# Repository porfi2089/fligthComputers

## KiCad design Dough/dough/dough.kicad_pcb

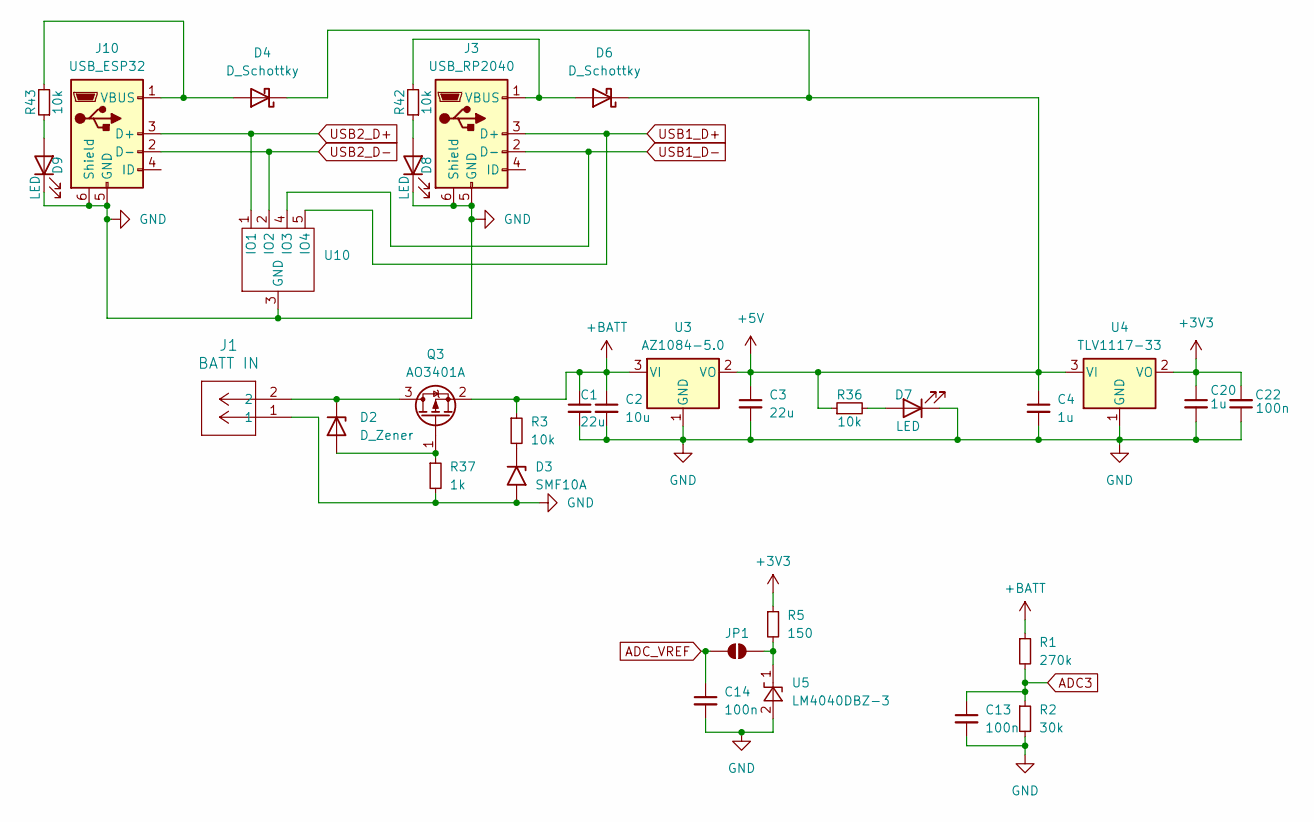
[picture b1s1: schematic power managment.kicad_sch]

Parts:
C1, C3: 22u; C_0603_1608Metric_Pad1.08x0.95mm_HandSolder
C2: 10u; C_0603_1608Metric_Pad1.08x0.95mm_HandSolder
C4, C20: 1u; C_0603_1608Metric_Pad1.08x0.95mm_HandSolder
C13, C14, C22: 100n; C_0603_1608Metric_Pad1.08x0.95mm_HandSolder
D2: D_Zener; D_SOD-123
D3: SMF10A; D_SMF
D4, D6: D_Schottky; D_SOD-323_HandSoldering
D7, D8, D9: LED; LED_0603_1608Metric_Pad1.05x0.95mm_HandSolder
J1: BATT IN; CONN2_H-B-02-TS_ADM
J3: USB_RP2040; USB_Micro-B_Amphenol_10118194_Horizontal
J10: USB_ESP32; USB_Micro-B_Amphenol_10118194_Horizontal
JP1: SolderJumper-2_P1.3mm_Open_TrianglePad1.0x1.5mm
Q3: AO3401A; SOT-23_Handsoldering
R1: 270k; R_0603_1608Metric_Pad0.98x0.95mm_HandSolder
R2: 30k; R_0603_1608Metric_Pad0.98x0.95mm_HandSolder
R3, R36, R42, R43: 10k; R_0603_1608Metric_Pad0.98x0.95mm_HandSolder
R5: 150; R_0603_1608Metric_Pad0.98x0.95mm_HandSolder
R37: 1k; R_0603_1608Metric_Pad0.98x0.95mm_HandSolder
U3: AZ1084-5.0; TO-252-3_TabPin2
U4: TLV1117-33; SOT-223-3_TabPin2
U5: LM4040DBZ-3; SOT-23
U10: 10-UFDNF(2.5mm-1mm)

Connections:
+3V3: C20.1, C22.2, R5.1, U4.2 (VO); also elsewhere on the board
+5V: C3.1, C4.1, D4.1 (K), D6.1 (K), R36.1, U3.2 (VO), U4.3 (VI); also elsewhere on the board
+BATT: C1.1, C2.1, Q3.2 (S), R1.1, R3.1, U3.3 (VI); also elsewhere on the board
ADC3: C13.1, R1.2, R2.1; also elsewhere on the board
ADC_VREF: C14.1, JP1.1 (A); also elsewhere on the board
unnamed: D2.2 (A), Q3.1 (G), R37.1
unnamed: D2.1 (K), J1.2, Q3.3 (D)
unnamed: D3.1 (A1), R3.2
unnamed: D4.2 (A), J10.1 (VBUS), R43.2
unnamed: D6.2 (A), J3.1 (VBUS), R42.2
unnamed: D7.2 (A), R36.2
unnamed: D8.2 (A), R42.1
unnamed: D9.2 (A), R43.1
unnamed: JP1.2 (B), R5.2, U5.1 (K)
USB1_D+: J3.3 (D+), U10.5 (IO4); also elsewhere on the board
USB1_D-: J3.2 (D-), U10.4 (IO3); also elsewhere on the board
USB2_D+: J10.3 (D+), U10.1 (IO1); also elsewhere on the board
USB2_D-: J10.2 (D-), U10.2 (IO2); also elsewhere on the board

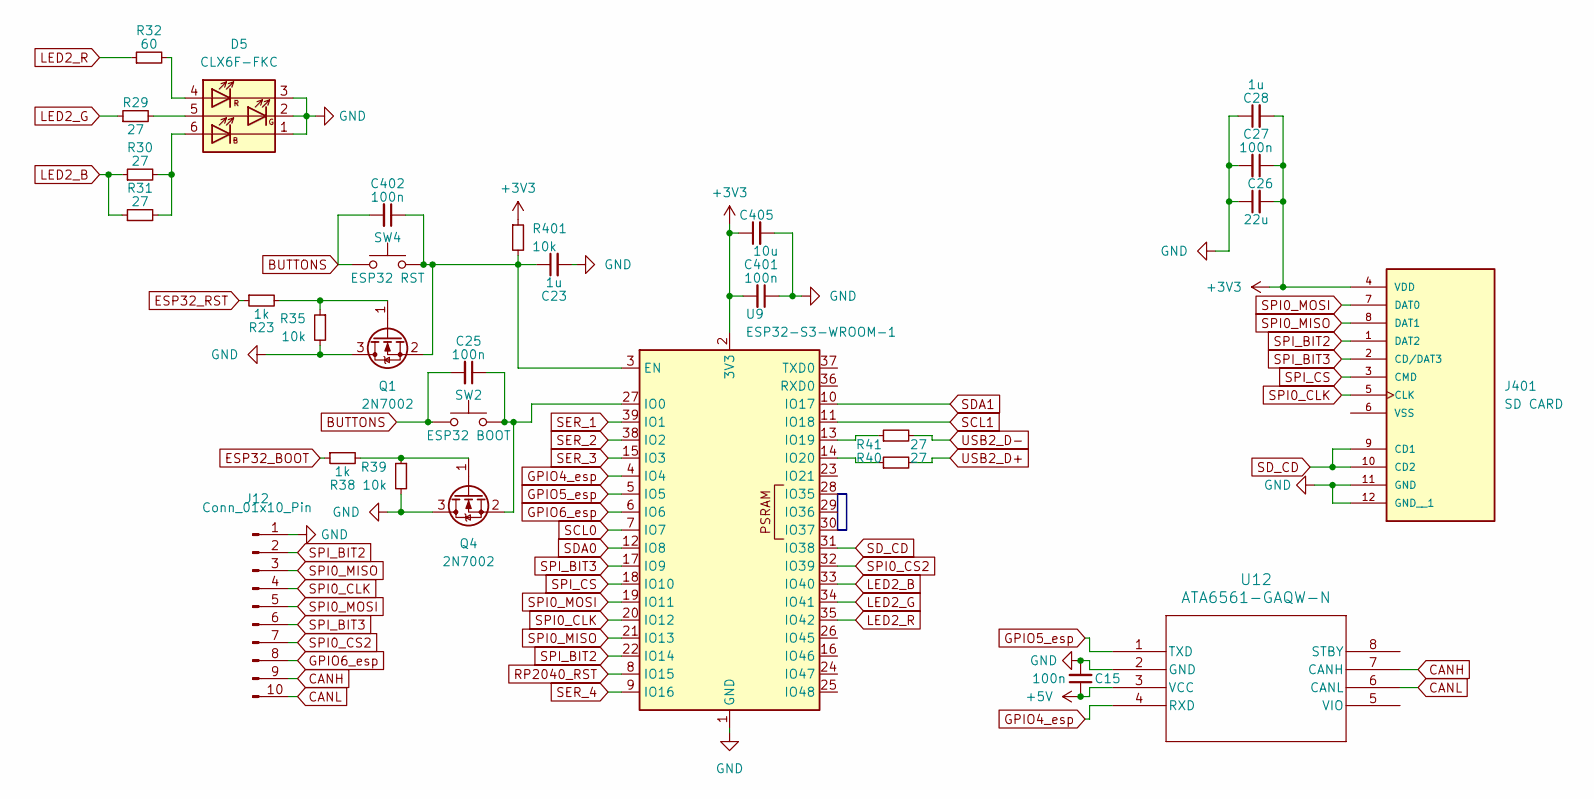
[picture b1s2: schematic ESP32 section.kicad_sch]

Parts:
C15, C25, C27, C401, C402: 100n; C_0603_1608Metric_Pad1.08x0.95mm_HandSolder
C23, C28: 1u; C_0603_1608Metric_Pad1.08x0.95mm_HandSolder
C26: 22u; C_0603_1608Metric_Pad1.08x0.95mm_HandSolder
C405: 10u; C_0603_1608Metric_Pad1.08x0.95mm_HandSolder
D5: CLX6F-FKC; LED_RGB_PLCC-6
J12: Conn_01x10_Pin; PinHeader_1x10_P2.54mm_Vertical
J401: SD CARD; MSD11_card_conn
Q1, Q4: 2N7002; SOT-23
R23, R38: 1k; R_0603_1608Metric_Pad0.98x0.95mm_HandSolder
R29, R30, R31, R40, R41: 27; R_0603_1608Metric_Pad0.98x0.95mm_HandSolder
R32: 60; R_0603_1608Metric_Pad0.98x0.95mm_HandSolder
R35, R39, R401: 10k; R_0603_1608Metric_Pad0.98x0.95mm_HandSolder
SW2: ESP32 BOOT; SW_Tactile_SPST_NO_Straight_CK_PTS636Sx25SMTRLFS
SW4: ESP32 RST; SW_Tactile_SPST_NO_Straight_CK_PTS636Sx25SMTRLFS
U9: ESP32-S3-WROOM-1
U12: ATA6561-GAQW-N; SOIC8_4P9X3P9MC_MCH

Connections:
+3V3: C26.2, C27.1, C28.2, C401.2, C405.1, J401.4 (VDD), R401.1, U9.2 (3V3); also elsewhere on the board
+5V: C15.1, U12.3 (VCC); also elsewhere on the board
BUTTONS: C25.2, C402.2, SW2.1, SW4.1; also elsewhere on the board
CANH: J12.9, U12.7 (CANH)
CANL: J12.10, U12.6 (CANL)
ESP32_BOOT: R38.1; also elsewhere on the board
ESP32_RST: R23.1; also elsewhere on the board
GPIO4_esp: U9.4 (IO4), U12.4 (RXD)
GPIO5_esp: U9.5 (IO5), U12.1 (TXD)
GPIO6_esp: J12.8, U9.6 (IO6)
LED2_B: R30.1, R31.1, U9.33 (IO40)
LED2_G: R29.1, U9.34 (IO41)
LED2_R: R32.1, U9.35 (IO42)
unnamed: D5.6 (AB), R30.2, R31.2
unnamed: D5.5 (AG), R29.2
unnamed: D5.4 (AR), R32.2
unnamed: C23.1, C402.1, Q1.2 (S), R401.2, SW4.2, U9.3 (EN)
unnamed: C25.1, Q4.2 (S), SW2.2, U9.27 (IO0)
unnamed: R41.1, U9.13 (IO19)
unnamed: R40.1, U9.14 (IO20)
RP2040_RST: U9.8 (IO15); also elsewhere on the board
SCL0: U9.7 (IO7); also elsewhere on the board
SCL1: U9.11 (IO18); also elsewhere on the board
SDA0: U9.12 (IO8); also elsewhere on the board
SDA1: U9.10 (IO17); also elsewhere on the board
SD_CD: J401.9 (CD1), J401.10 (CD2), U9.31 (IO38)
SER_1: U9.39 (IO1); also elsewhere on the board
SER_2: U9.38 (IO2); also elsewhere on the board
SER_3: U9.15 (IO3); also elsewhere on the board
SER_4: U9.9 (IO16); also elsewhere on the board
SPI0_CLK: J12.4, J401.5 (CLK), U9.20 (IO12)
SPI0_CS2: J12.7, U9.32 (IO39)
SPI0_MISO: J12.3, J401.8 (DAT1), U9.21 (IO13)
SPI0_MOSI: J12.5, J401.7 (DAT0), U9.19 (IO11)
SPI_BIT2: J12.2, J401.1 (DAT2), U9.22 (IO14)
SPI_BIT3: J12.6, J401.2 (CD/DAT3), U9.17 (IO9)
SPI_CS: J401.3 (CMD), U9.18 (IO10)
USB2_D+: R40.2; also elsewhere on the board
USB2_D-: R41.2; also elsewhere on the board

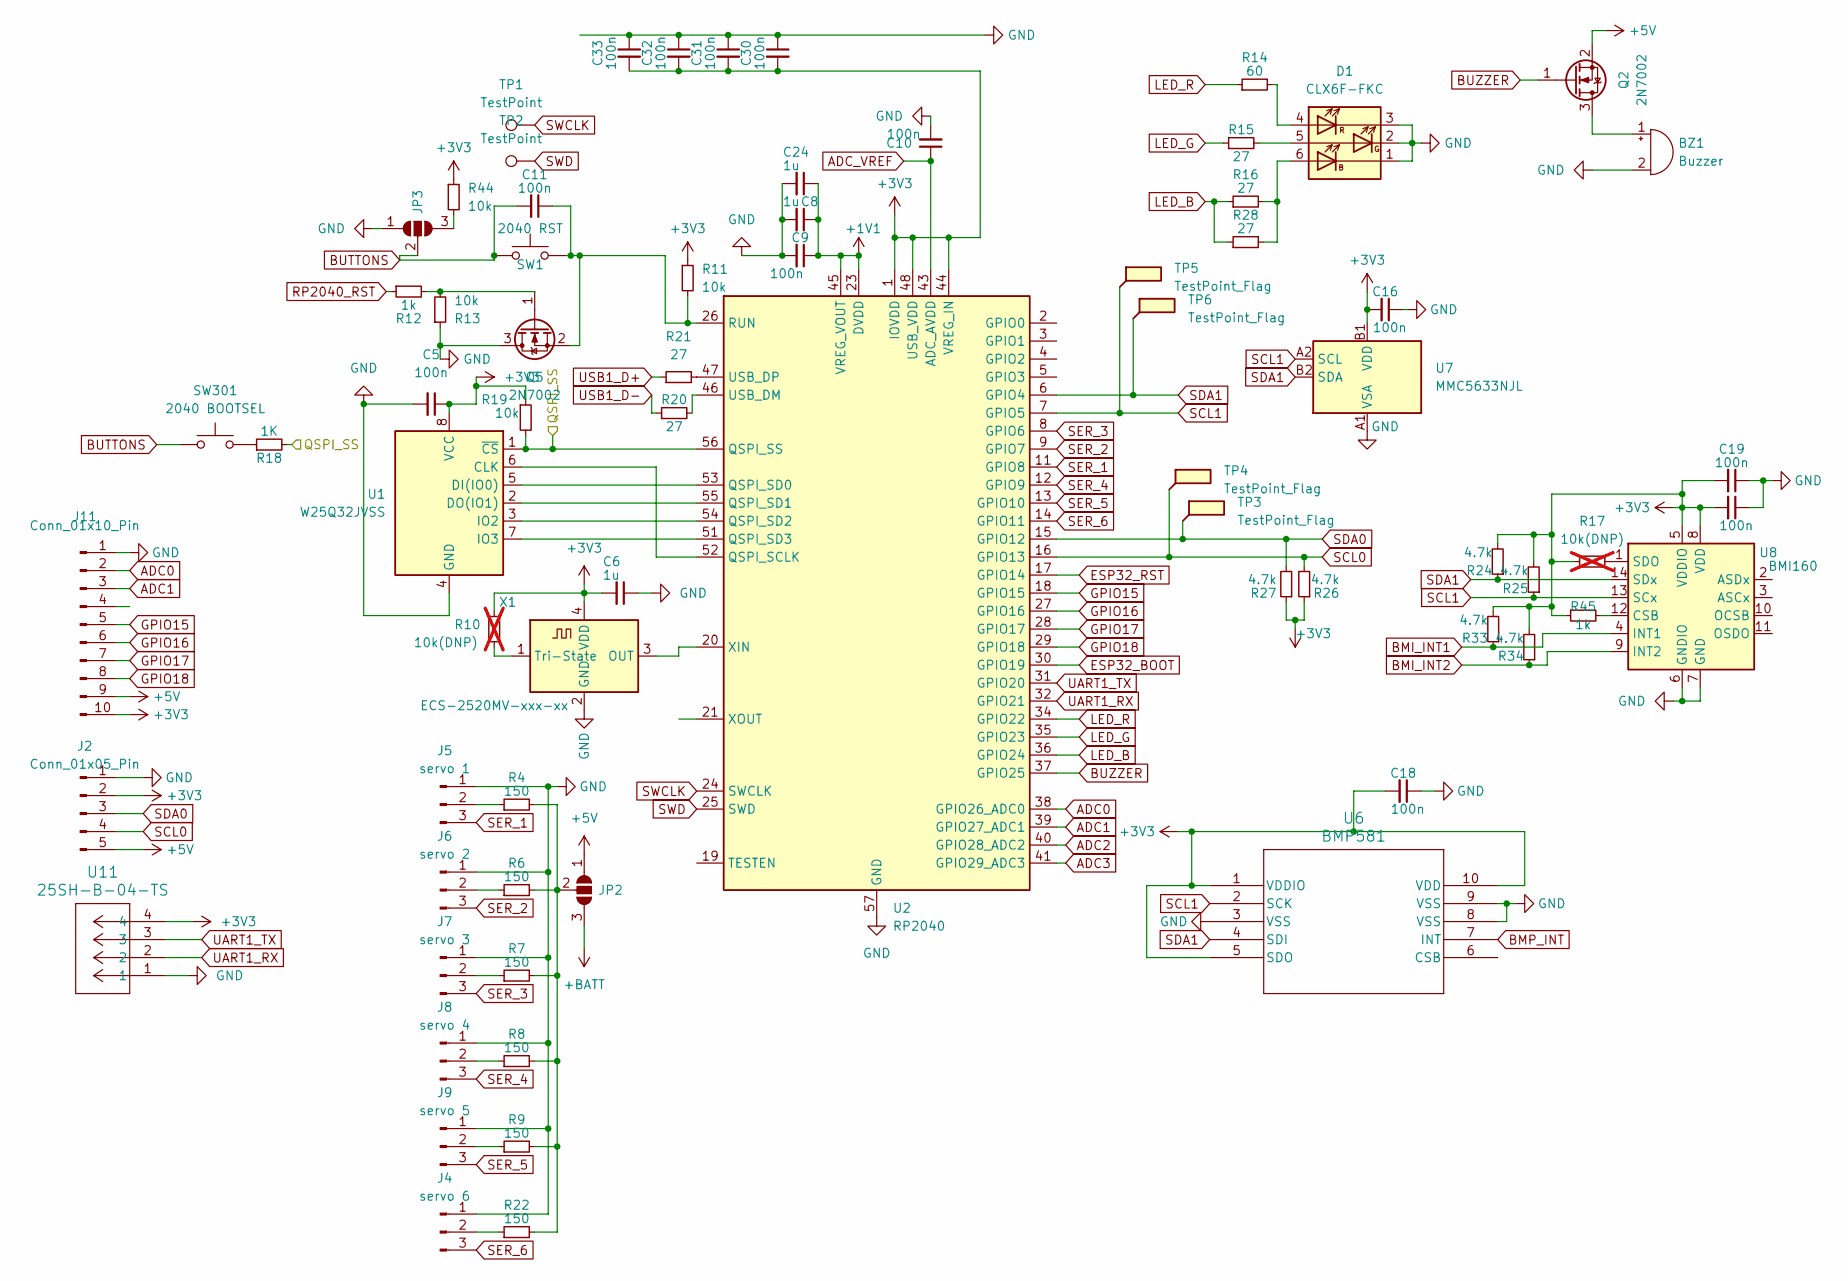
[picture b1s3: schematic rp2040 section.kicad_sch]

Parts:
BZ1: Buzzer; Buzzer_CUI_CPT-9019S-SMT
C5, C9, C10, C11, C12, C16, C18, C19, C30, C31, C32, C33: 100n; C_0603_1608Metric_Pad1.08x0.95mm_HandSolder
C6, C8, C24: 1u; C_0603_1608Metric_Pad1.08x0.95mm_HandSolder
D1: CLX6F-FKC; LED_RGB_PLCC-6
J2: Conn_01x05_Pin; PinHeader_1x05_P2.54mm_Vertical
J4: servo 6; PinHeader_1x03_P2.54mm_Vertical
J5: servo 1; PinHeader_1x03_P2.54mm_Vertical
J6: servo 2; PinHeader_1x03_P2.54mm_Vertical
J7: servo 3; PinHeader_1x03_P2.54mm_Vertical
J8: servo 4; PinHeader_1x03_P2.54mm_Vertical
J9: servo 5; PinHeader_1x03_P2.54mm_Vertical
J11: Conn_01x10_Pin; PinHeader_1x10_P2.54mm_Vertical
JP2, JP3: SolderJumper-3_P1.3mm_Open_RoundedPad1.0x1.5mm
Q2, Q5: 2N7002; SOT-23
R4, R6, R7, R8, R9, R22: 150; R_0603_1608Metric_Pad0.98x0.95mm_HandSolder
R10, R17: 10k(DNP); R_0603_1608Metric_Pad0.98x0.95mm_HandSolder; not fitted
R11, R13, R19, R44: 10k; R_0603_1608Metric_Pad0.98x0.95mm_HandSolder
R12, R45: 1k; R_0603_1608Metric_Pad0.98x0.95mm_HandSolder
R14: 60; R_0603_1608Metric_Pad0.98x0.95mm_HandSolder
R15, R16, R20, R21, R28: 27; R_0603_1608Metric_Pad0.98x0.95mm_HandSolder
R18: 1K; R_0603_1608Metric_Pad0.98x0.95mm_HandSolder
R24, R25, R26, R27, R33, R34: 4.7k; R_0603_1608Metric_Pad0.98x0.95mm_HandSolder
SW1: 2040 RST; SW_Tactile_SPST_NO_Straight_CK_PTS636Sx25SMTRLFS
SW301: 2040 BOOTSEL; SW_Tactile_SPST_NO_Straight_CK_PTS636Sx25SMTRLFS
TP1, TP2: TestPoint; TestPoint_Pad_D1.5mm
TP3, TP4, TP5, TP6: TestPoint_Flag; TestPoint_Pad_1.5x1.5mm
U1: W25Q32JVSS; SOIC-8_5.23x5.23mm_P1.27mm
U2: RP2040; QFN-56-1EP_7x7mm_P0.4mm_EP3.2x3.2mm
U6: BMP581; QFN10_BMP581_BOS
U7: MMC5633NJL; WLP-4_0.86x0.86mm_P0.4mm
U8: BMI160; Bosch_LGA-14_3x2.5mm_P0.5mm
U11: 25SH-B-04-TS; CONN_25SH-B-04-TS_ADM
X1: ECS-2520MV-xxx-xx; Oscillator_SMD_ECS_2520MV-xxx-xx-4Pin_2.5x2.0mm

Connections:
+1V1: C8.1, C9.1, C24.1, U2.23 (DVDD), U2.45 (VREG_VOUT), U2.50 (DVDD)
+3V3: C5.1, C6.2, C12.2, C16.2, C18.2, C19.2, C30.2, C31.2, C32.2, C33.2, J2.2, J11.10, R10.1, R11.1, R17.1, R19.1, R24.2, R25.2, R26.1, R27.1, R33.2, R34.2, R44.1, R45.1, U1.8 (VCC), U2.1 (IOVDD), U2.10 (IOVDD), U2.22 (IOVDD), U2.33 (IOVDD), U2.42 (IOVDD), U2.44 (VREG_IN), U2.48 (USB_VDD), U2.49 (IOVDD), U6.1 (VDDIO), U6.5 (SDO), U6.10 (VDD), U7.B1 (VDD), U8.5 (VDDIO), U8.8 (VDD), U11.4, X1.4 (VDD); also elsewhere on the board
+5V: J2.5, J11.9, JP2.1 (A), Q2.2 (S); also elsewhere on the board
+BATT: JP2.3 (B); also elsewhere on the board
/RP2040 section/QSPI_SS: R18.2, R19.2, U1.1 (~CS), U2.56 (QSPI_SS)
ADC0: J11.2, U2.38 (GPIO26_ADC0)
ADC1: J11.3, U2.39 (GPIO27_ADC1)
ADC2: U2.40 (GPIO28_ADC2); also elsewhere on the board
ADC3: U2.41 (GPIO29_ADC3); also elsewhere on the board
ADC_VREF: C10.1, U2.43 (ADC_AVDD); also elsewhere on the board
BMI_INT1: R33.1, U8.4 (INT1)
BMI_INT2: R34.1, U8.9 (INT2)
BMP_INT: U6.7 (INT)
BUTTONS: C11.2, JP3.2 (C), SW1.1, SW301.1; also elsewhere on the board
BUZZER: Q2.1 (G), U2.37 (GPIO25)
ESP32_BOOT: U2.30 (GPIO19); also elsewhere on the board
ESP32_RST: U2.17 (GPIO14); also elsewhere on the board
GPIO15: J11.5, U2.18 (GPIO15)
GPIO16: J11.6, U2.27 (GPIO16)
GPIO17: J11.7, U2.28 (GPIO17)
GPIO18: J11.8, U2.29 (GPIO18)
LED_B: R16.1, R28.1, U2.36 (GPIO24)
LED_G: R15.1, U2.35 (GPIO23)
LED_R: R14.1, U2.34 (GPIO22)
unnamed: BZ1.1 (+), Q2.3 (D)
unnamed: D1.6 (AB), R16.2, R28.2
unnamed: D1.5 (AG), R15.2
unnamed: D1.4 (AR), R14.2
unnamed: J4.2, R22.1
unnamed: J5.2, R4.1
unnamed: J6.2, R6.1
unnamed: J7.2, R7.1
unnamed: J8.2, R8.1
unnamed: J9.2, R9.1
unnamed: JP2.2 (C), R4.2, R6.2, R7.2, R8.2, R9.2, R22.2
unnamed: JP3.3 (B), R44.2
unnamed: Q5.1 (G), R12.2, R13.2
unnamed: C11.1, Q5.2 (S), R11.2, SW1.2, U2.26 (RUN)
unnamed: R18.1, SW301.2
unnamed: U1.6 (CLK), U2.52 (QSPI_SCLK)
unnamed: U1.5 (DI(IO0)), U2.53 (QSPI_SD0)
unnamed: U1.2 (DO(IO1)), U2.55 (QSPI_SD1)
unnamed: U1.3 (IO2), U2.54 (QSPI_SD2)
unnamed: U1.7 (IO3), U2.51 (QSPI_SD3)
unnamed: R20.2, U2.46 (USB_DM)
unnamed: R21.2, U2.47 (USB_DP)
unnamed: U2.20 (XIN), X1.3 (OUT)
unnamed: R45.2, U8.12 (CSB)
unnamed: R17.2, U8.1 (SDO)
unnamed: R10.2, X1.1 (Tri-State)
RP2040_RST: R12.1; also elsewhere on the board
SCL0: J2.4, R26.2, TP4.1, U2.16 (GPIO13); also elsewhere on the board
SCL1: R25.1, TP5.1, U2.7 (GPIO5), U6.2 (SCK), U7.A2 (SCL), U8.13 (SCx); also elsewhere on the board
SDA0: J2.3, R27.2, TP3.1, U2.15 (GPIO12); also elsewhere on the board
SDA1: R24.1, TP6.1, U2.6 (GPIO4), U6.4 (SDI), U7.B2 (SDA), U8.14 (SDx); also elsewhere on the board
SER_1: J5.3, U2.11 (GPIO8); also elsewhere on the board
SER_2: J6.3, U2.9 (GPIO7); also elsewhere on the board
SER_3: J7.3, U2.8 (GPIO6); also elsewhere on the board
SER_4: J8.3, U2.12 (GPIO9); also elsewhere on the board
SER_5: J9.3, U2.13 (GPIO10)
SER_6: J4.3, U2.14 (GPIO11)
SWCLK: TP1.1, U2.24 (SWCLK)
SWD: TP2.1, U2.25 (SWD)
UART1_RX: U2.32 (GPIO21), U11.2
UART1_TX: U2.31 (GPIO20), U11.3
USB1_D+: R21.1; also elsewhere on the board
USB1_D-: R20.1; also elsewhere on the board

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
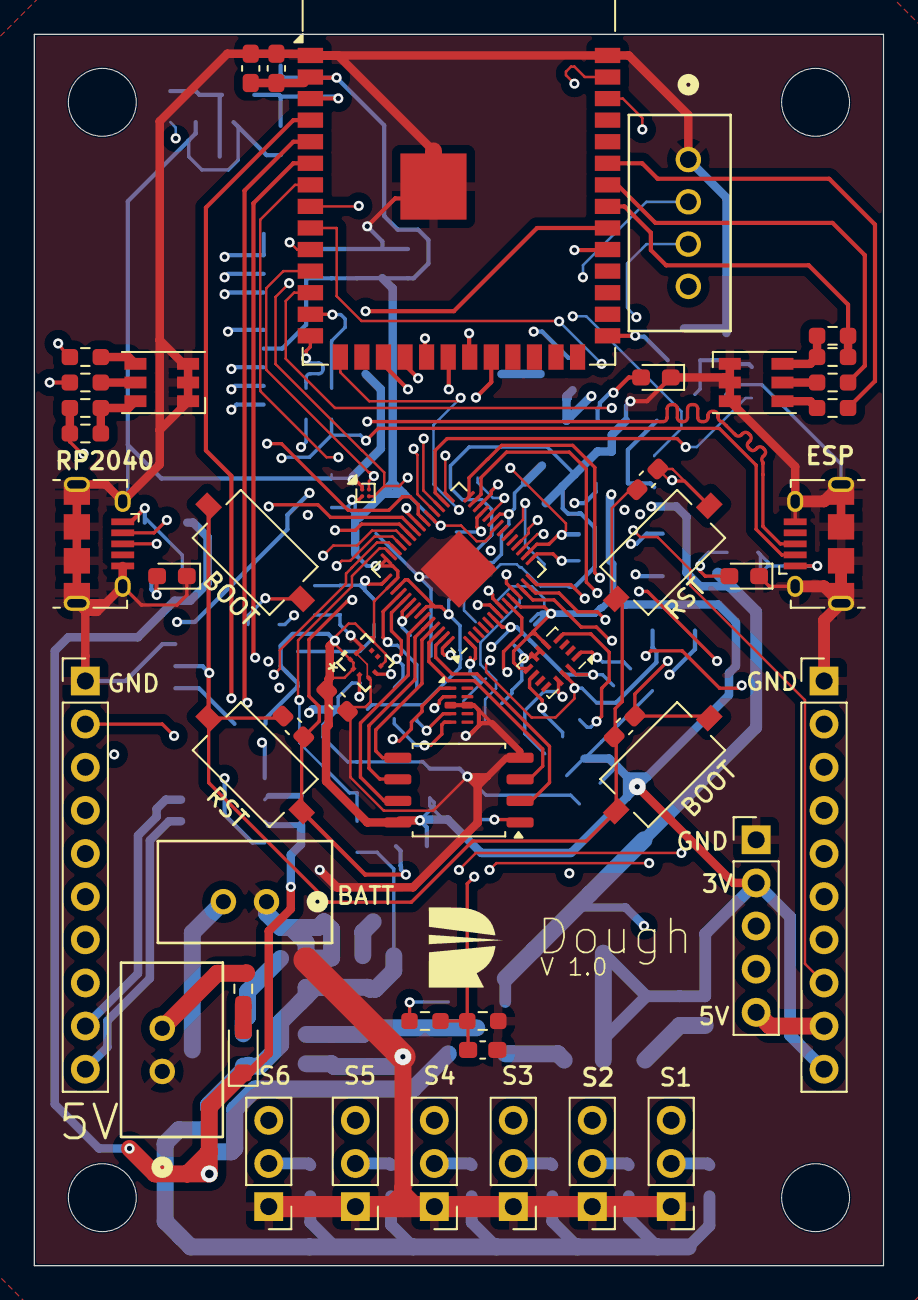
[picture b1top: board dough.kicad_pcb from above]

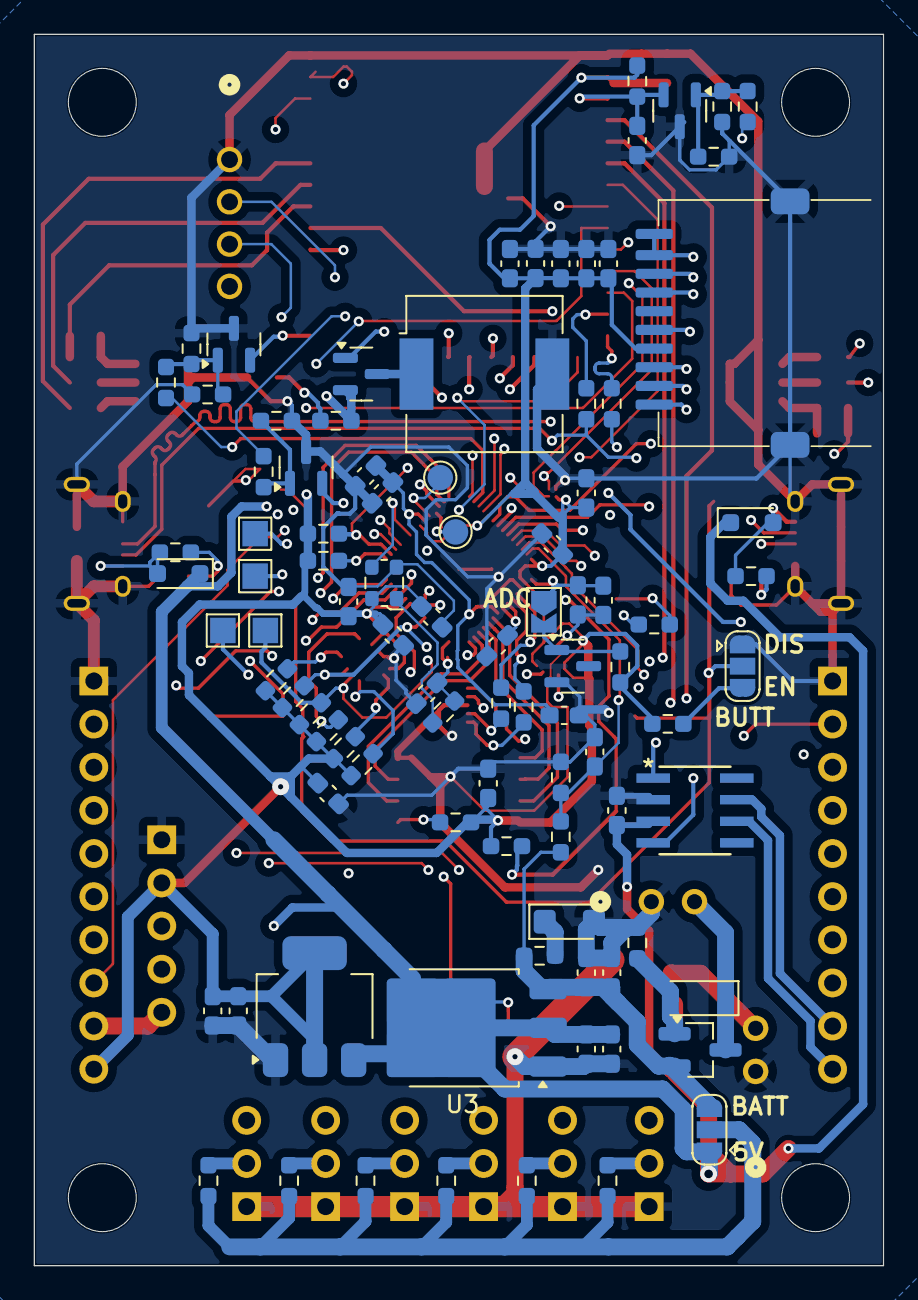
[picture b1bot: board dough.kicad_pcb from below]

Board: 4 copper layers, 50.0 x 72.5 mm, 143 parts (93 on the bottom side), 105 nets.

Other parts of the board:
C7: 100n; C_0603_1608Metric_Pad1.08x0.95mm_HandSolder
C403, C404: 22u; C_0603_1608Metric_Pad1.08x0.95mm_HandSolder
D10: D_Schottky; D_SOD-323_HandSoldering
J13: 5v; CONN2_H-B-02-TS_ADM
R35#2, R39#2, R46, R48: 10k; R_0603_1608Metric_Pad0.98x0.95mm_HandSolder
R47: SDNT1608; R_0603_1608Metric_Pad0.98x0.95mm_HandSolder
_: LOGO

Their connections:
+3V3: C403.2, C404.2; also elsewhere on the board
+5V: D10.1 (K), R46.1; also elsewhere on the board
ADC2: C7.1, R46.2, R47.1; also elsewhere on the board
unnamed: D10.2 (A), R48.2
unnamed: J13.2, R48.1

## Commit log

2024-05-30 started routing
2024-06-07 pre prod 1
2024-06-29 V1.0 pre prod
2024-08-20 dough First production run
